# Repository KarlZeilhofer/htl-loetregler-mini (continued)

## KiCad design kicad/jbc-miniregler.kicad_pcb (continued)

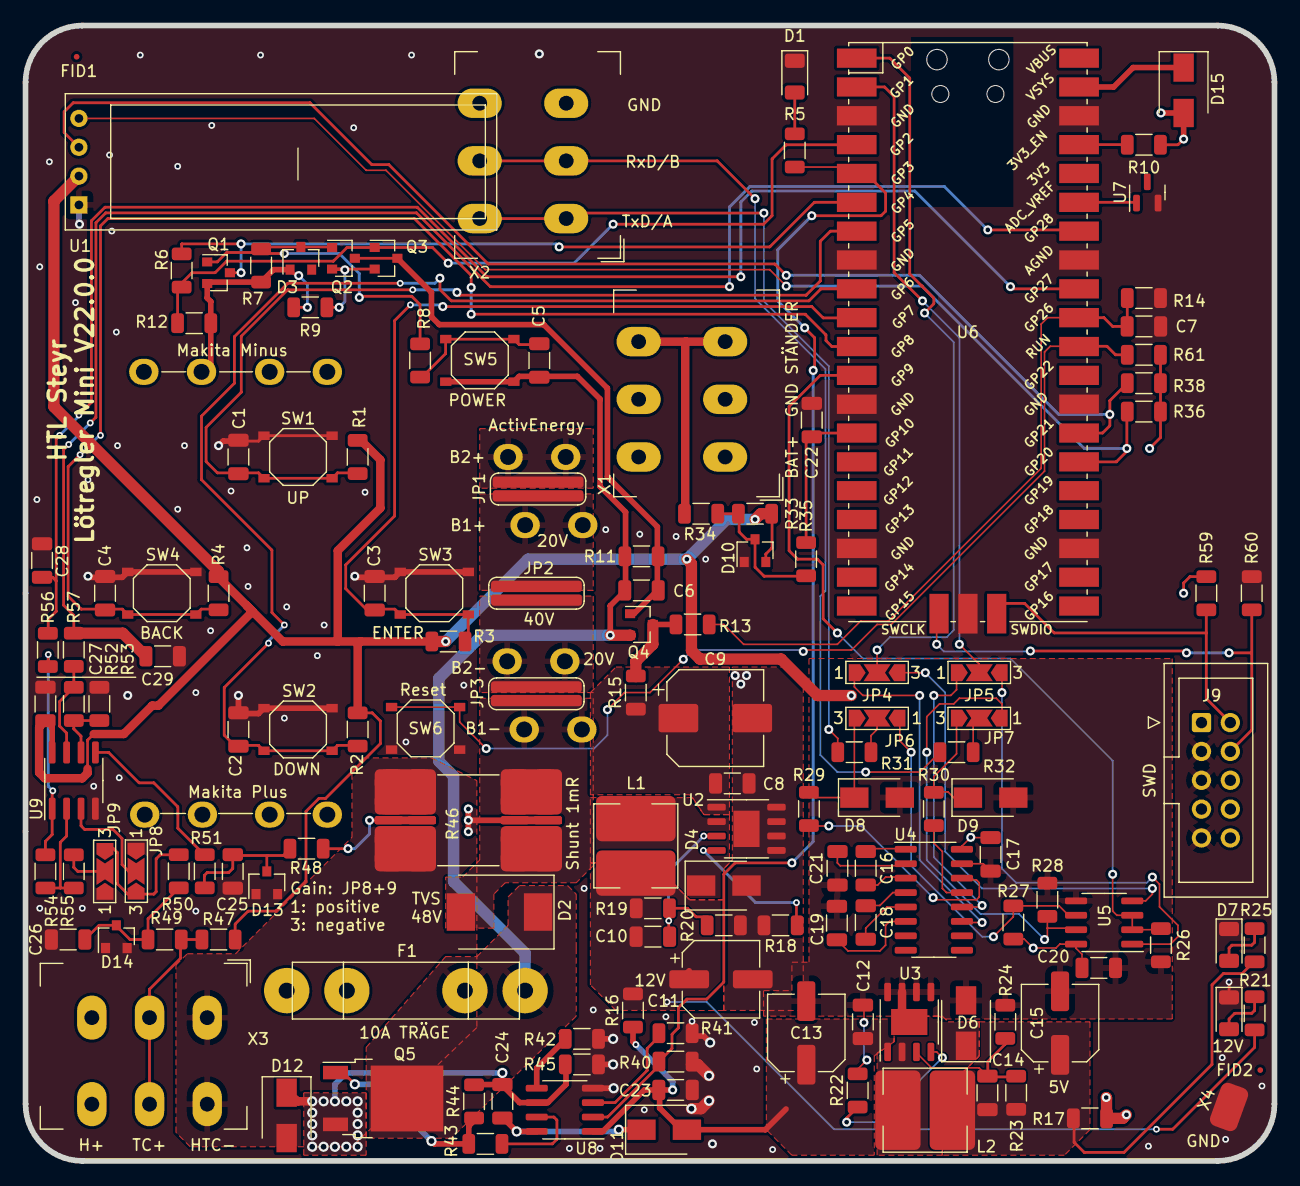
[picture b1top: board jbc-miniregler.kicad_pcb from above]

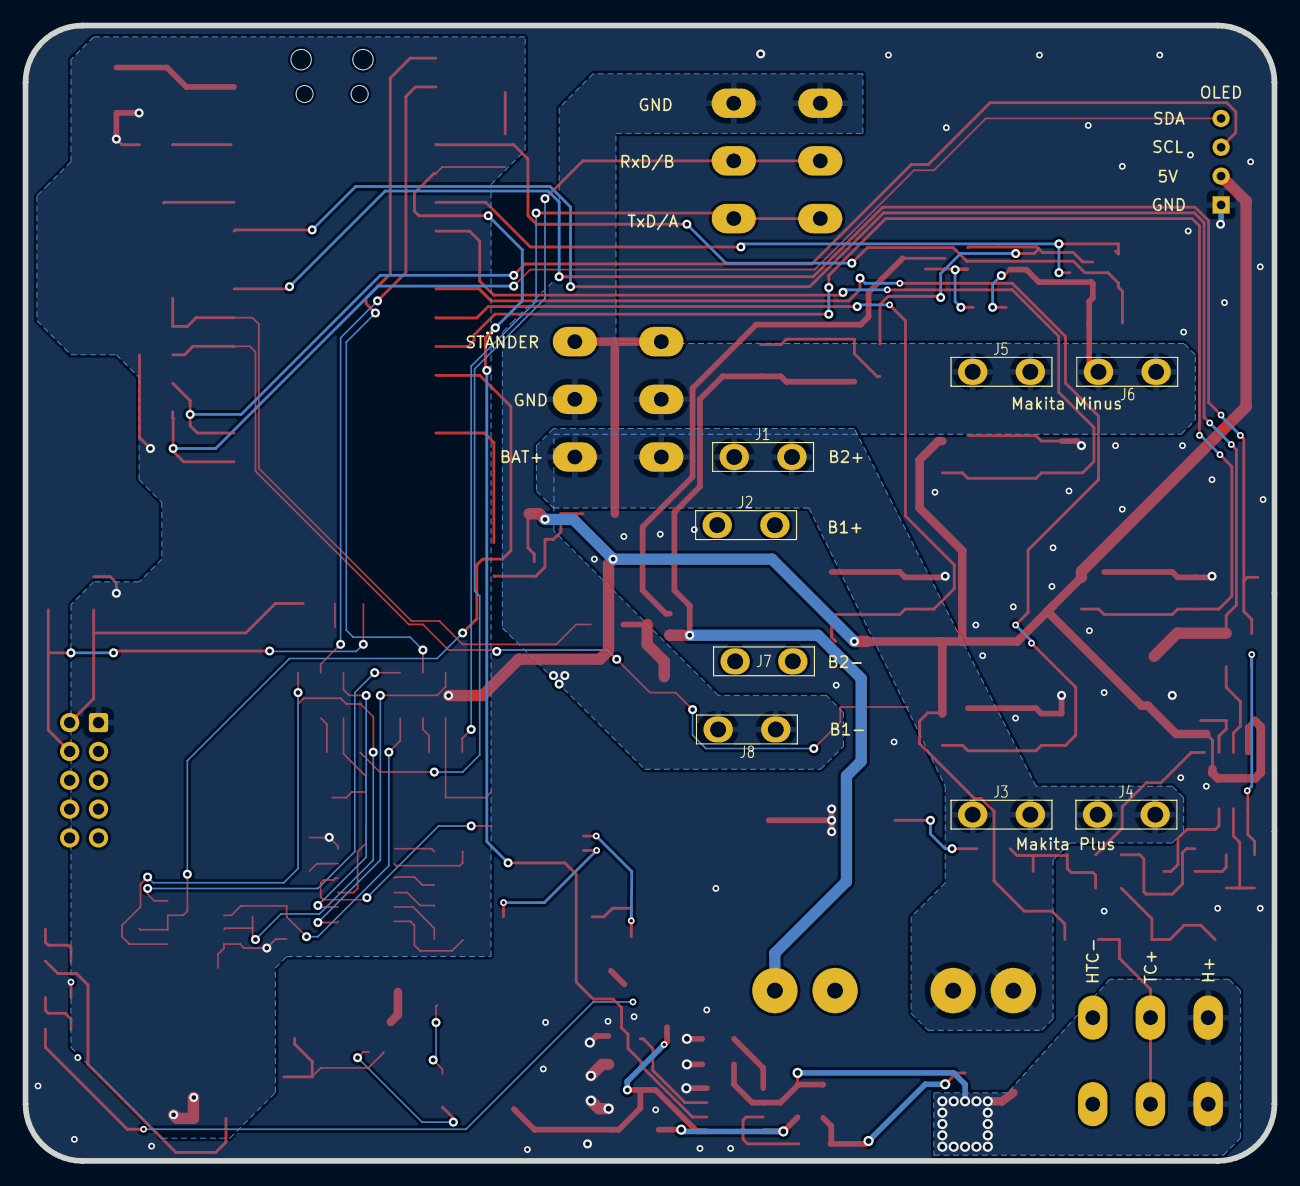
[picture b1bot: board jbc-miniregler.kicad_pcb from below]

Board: 2 copper layers, 110.0 x 100.0 mm, 154 parts (8 on the bottom side), 88 nets.

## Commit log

2021-05-02 Erste Schaltplanversion, BOM ist noch fertigzustellen
2021-05-02 BOM ist nun fast fertig
2021-05-04 BOM Fertig, 3D auch fast fertig. Ein paar Footrpints fehlen noch.
2021-05-07 kleinere Updates im Schaltplan
2021-05-07 Reviews und ein paar Verbesserungen
2021-05-18 um Option RS485 erweitert
2021-05-21 Layout
2021-05-28 WIP Layout, TODO: DRC
2021-05-28 DRC clear
2021-05-28 Layout Fertig, TODOs: Beschriftungen fertig stellen, ...
    RS485 TVS-Diode
2021-05-29 OPV-Polaritätsoption, Zusatzfilter und Strombegrenzung
2021-05-29 vor "update all footprints", FP-Lib Version V5.10
2021-05-29 Neu: Spannungsreferenz TL431, Laout Fertig, TODO: Labels
2021-06-01 Bestellte Version v21.0.0
2021-06-01 postcommit
2021-06-09 Leitwert Edelstahl
2021-06-09 Griffstück Design und elastische Durchbiegung
2021-06-11 Neues Federkontaktdesign by Tobias Mit.
2021-06-14 html-bom
2021-06-14 Federkontakte: Design v1 thoretisch fertig, Tiefziehform noch in Arbeit
2021-06-15 Buchsenleist für OLED hinzugefügt
2021-06-16 WIP: erste Schritte der Firmware
2021-06-17 Anfrage Laserzuschnitt
2021-06-17 Hardware-Anpassungen bei Inbetriebnahme und Firmwareaktualisierung
2021-06-18 HTML-BOM aktualisiert
2021-06-21 Griffstück, erste 2 prototypen v0.01 und v0.03 gedruckt, TODO...
    Heizung muss gegenüber Sensor voreilend sein.
    Gatetreiber ist beim Umstecken drauf gegangen.
2021-06-21 Tiefzieform für Laserbleche optimiert
    postcommit
2021-06-23 Ausgabe der Temperatur über UART
2021-06-23 Gehäuseboden v0 für ActivEnergy
2021-06-23 Batteriearrektierung abgedeckt, USB-Ausschnitt optimiert
2021-06-24 gehäuse wand und deckel v1
2021-06-25 gcodes gelöscht
2021-07-01 Gehäusewand v2
2021-07-02 Bugfix: Schottky-Diode im Schaltplan
2021-07-02 Fingerkuppenring
2021-07-05 Tasterverbindung hinzugefügt
2021-07-05 ActivEnergy Batterieschuh
2021-07-05 Prusa Gehäusewand v2 nun mit Brim
2021-07-06 ActivEnergy Schuh v2
2021-09-22 wip, bugfixes für v21.0.1
2021-09-29 Workaround zu Isssue#7, USB Bootproblem
2021-10-09 BOM aktualisiert, Zenerdiode: Pinout IPC-konform gestaltet, ...
    siehe https://gitlab.com/kicad/libraries/kicad-symbols/-/issues/3157
2021-10-09 Überdeckende Footprints noch auseinander gerückt, ...
    HTML-Bom Export und Gerber-Export, 40 Stück bestell bei MulitCB
2021-11-10 Notizen, Kabelbelegung, Alternativbestückung
2021-11-10 Changelog und Firmware WIP
2021-11-10 post commit
2021-11-11 Bootscreen, richtige Battzustandsanzeige, V_USB-Feedback
2021-11-22 3D-Teile erweitert
2021-11-24 zugentlastung und blindstopfen, Griffstück vereinfacht, TODO...
    Griffstück 6-Eckig gestalten, damit es sauber gedruckt werden kann.
2021-11-27 Berner Batterie, Deckel v2, Boden v3
2021-11-27 MOSFET Alternative
2021-11-27 Deckel v2
2021-11-27 griffstück v2
2021-11-27 Griffstück, erster Prototyp V2
2021-11-27 Griffstück, kleine Nachbesserung, TODO: STL-Export
2021-11-27 Griffstück V2.1 inkl. STL
2021-11-29 Optimierung Isolierkörper
2021-11-29 Firmware für 18V
2022-02-06 Batterieschuh LUX Tools 20V, 1.5Ah
2022-02-07 3D: Griffstück Komplettset, Makita V3, Readme und Changelog
2022-02-07 Kleine Anpassungen in KiCad-SCH und Firmware
2022-02-09 2D-Zeichnungen, Griffstück
2022-04-01 Zeichnungen, details verbessert
2022-04-04 ordner struktur in 3D verbessert
2022-04-04 Zeichnung Halbschale innen
2022-06-01 Firmware: Übertemperaturwächter, Arduino Libs
2022-06-01 Batterie: Bosch Professional 18V
2022-06-01 3D Druck optimiert
2022-06-26 Auto stash before merge of "main" and "origin/main"
2022-06-27 Einhell, fast korrekt
2022-06-27 Bosch professional
2022-06-27 ignore release
2022-06-27 Einhell v2
2022-06-27 Makita Boden, v4: Abstand der Batteriekontakte korrigiert auf 39mm
2022-06-27 LUX Tools 2Ah, V1
2022-06-27 LUX Tools 2Ah, Maße wesentlich korrigiert, V2
2022-06-27 Milwaukee M18, Batterieschuh
2022-06-27 Codier-Nut, Milwaukee
2022-06-27 kleinere Updates der 3D Files
2022-10-12 LUX Tools nun endlich fertig
2022-11-09 Zugentlastung V1.4, etwas schwergängiger und länger gemacht
2022-11-09 remove submodule
2022-12-21 doppelte Datei gelöscht
2023-02-15 Verbesserter 3D-Druck der Griffschale rund für Polycarbonat
2023-02-15 Präsentations-Poster
2023-02-15 ignore KiCad 6 Backups
2023-02-15 Import von Johannes Haas
2023-02-15 Schottky in Pico-Versorgung, VREF korrigiert auf 3.0V
2023-02-15 BOM auf Lieferbarkeit aktualisiert, TODO: DRC bereinigen
2023-02-21 DRC bereinigt
2023-03-01 post-commit
2023-03-01 PCB fertig. Platzierung verbessert (Federklemme unter OLED)
    Layout minimal verbessert
2023-03-08 Bemaßungen, 30 Stk. PCBs bestellt
2023-03-15 WIP Gehäuseanpassungen für Pico
2023-03-15 erste änderungen am Gehäuse für Pico, TODO: testen
2023-03-29 Gehäuse-Deckel V3, gefixt
2023-04-12 Externe Arduino Libs aktualisiert, behebt Compiler-Fehlermeldungen
    bezgl. progmem_read(...)
2023-04-12 Schaltplan v22.0.0 exportiert
2023-04-12 Firmware auf Pico portiert und getestet!
2023-04-12 Firmware Update V0.2: Leistungsanzeige, Wiedereinschalten beim Kühlen
    Credits to J. Haas and F. Kramlinger
2023-06-21 UF2 Binary für Pico erstellt
